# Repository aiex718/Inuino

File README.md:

# Inuino
An Arduino Uno compatible microcontroller dev board based on the ATmega644P / ATmega1284P, using official core inside Arduino IDE.

# Usage
Add this link to boards manager

<https://raw.githubusercontent.com/aiex718/Inuino/master/Release/package_inuino_index.json>

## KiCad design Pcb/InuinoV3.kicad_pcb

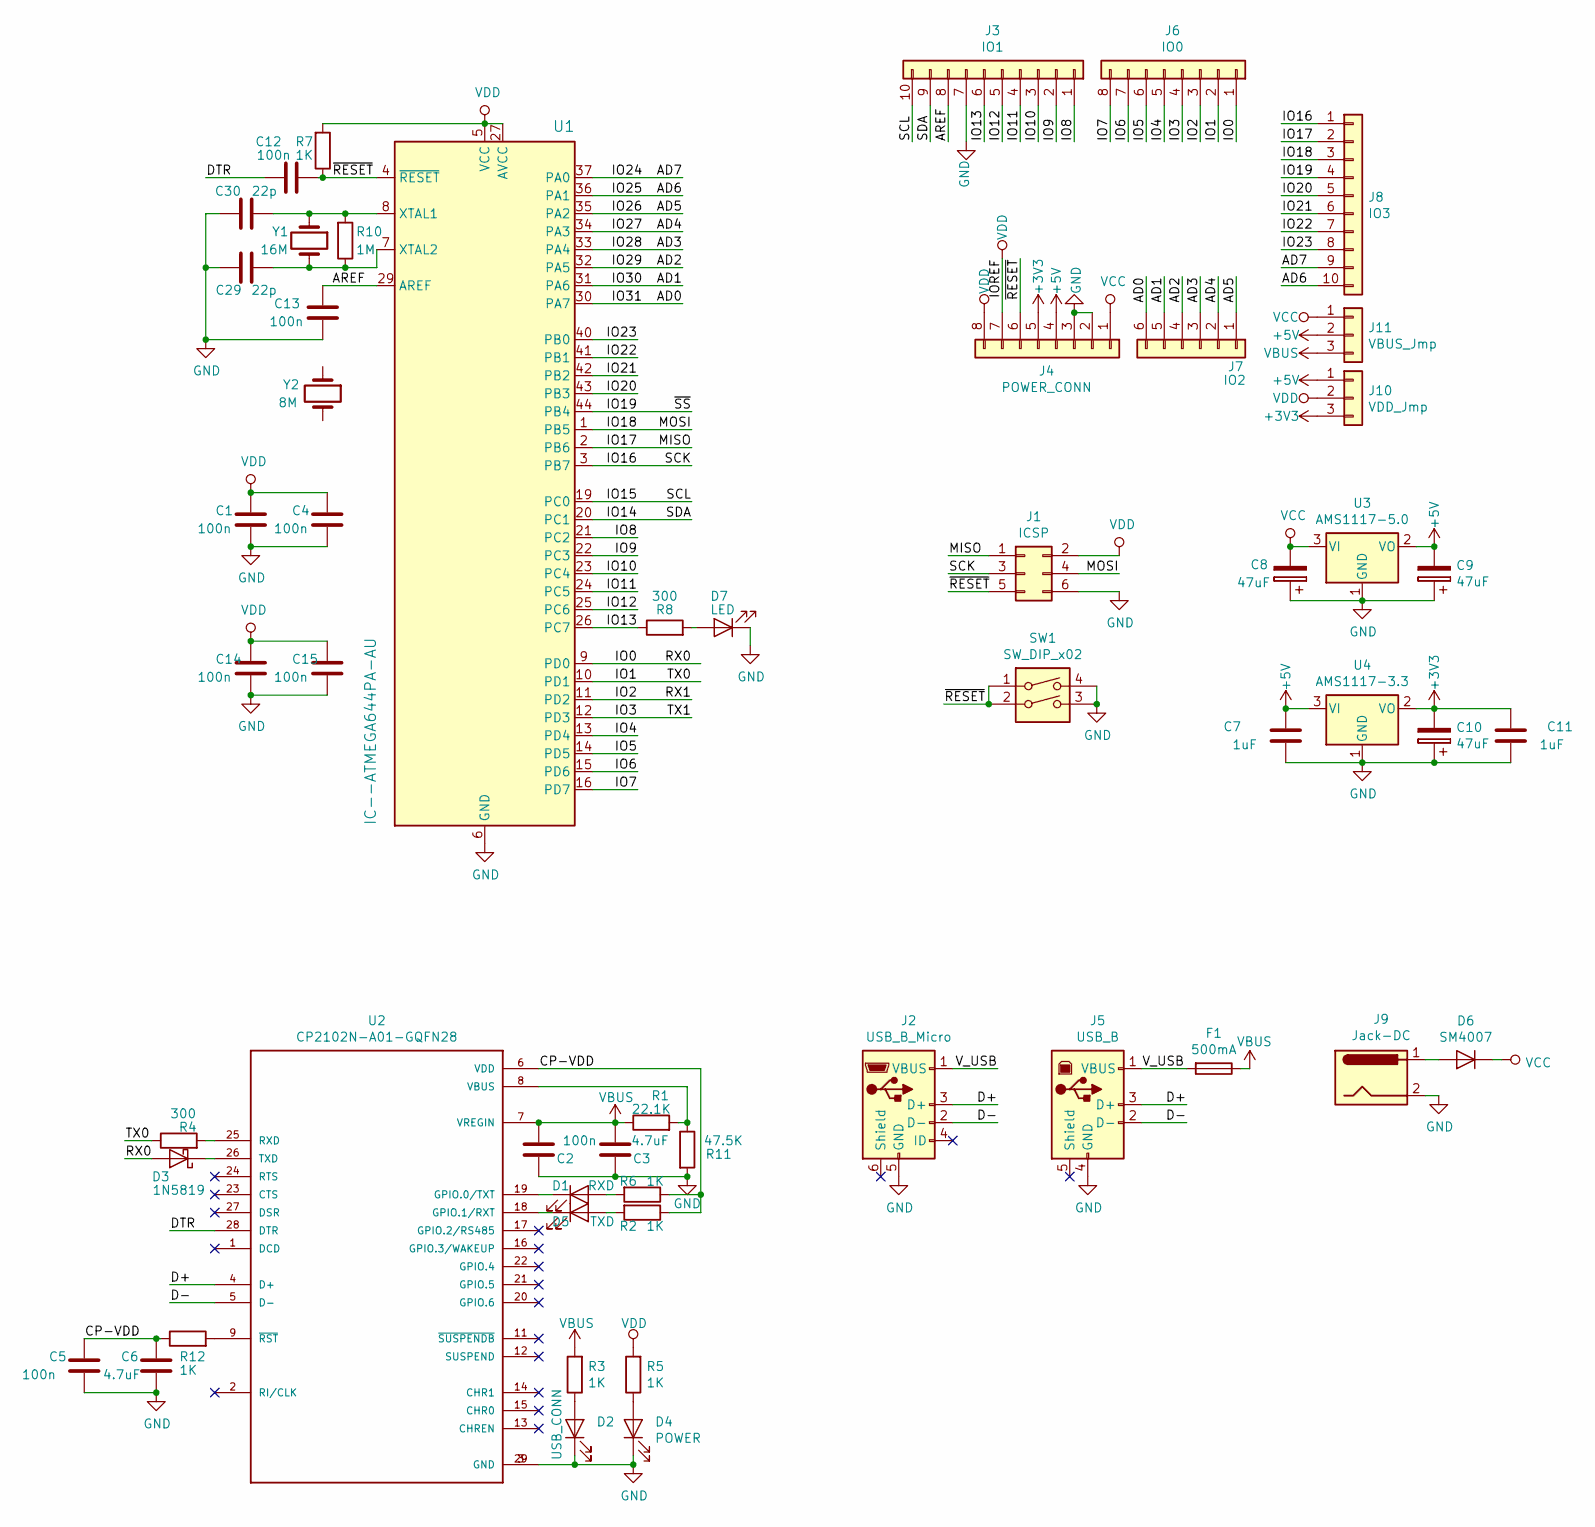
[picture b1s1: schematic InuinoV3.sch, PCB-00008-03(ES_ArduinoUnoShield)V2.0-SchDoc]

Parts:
C1, C2, C4, C5, C12, C13, C14, C15: 100n; C_0805_2012Metric_Pad1.15x1.40mm_HandSolder
C3, C6: 4.7uF; C_0805_2012Metric_Pad1.15x1.40mm_HandSolder
C7, C11: 1uF; C_0805_2012Metric_Pad1.15x1.40mm_HandSolder
C8, C9, C10: 47uF; CP_Radial_D6.3mm_P2.50mm
C29, C30: 22p; C_0805_2012Metric_Pad1.15x1.40mm_HandSolder
D1: RXD; LED_0805_2012Metric_Pad1.15x1.40mm_HandSolder
D2: USB_CONN; LED_0805_2012Metric_Pad1.15x1.40mm_HandSolder
D3: 1N5819; D_SMA_Handsoldering
D4: POWER; LED_0805_2012Metric_Pad1.15x1.40mm_HandSolder
D5: TXD; LED_0805_2012Metric_Pad1.15x1.40mm_HandSolder
D6: SM4007; D_SMA_Handsoldering
D7: LED; LED_0805_2012Metric_Pad1.15x1.40mm_HandSolder
F1: 500mA; Fuse_1812_4532Metric_Pad1.30x3.40mm_HandSolder
J1: ICSP; PinHeader_2x03_P2.54mm_Vertical
J2: USB_B_Micro; USB_Micro-B_Molex-105017-0001
J3: IO1; PinSocket_1x10_P2.54mm_Vertical
J4: POWER_CONN; PinSocket_1x08_P2.54mm_Vertical
J5: USB_B; USB_B_OST_USB-B1HSxx_Horizontal
J6: IO0; PinSocket_1x08_P2.54mm_Vertical
J7: IO2; PinSocket_1x06_P2.54mm_Vertical
J8: IO3; PinSocket_1x10_P2.54mm_Vertical
J9: Jack-DC; BarrelJack_Wuerth_6941xx301002
J10: VDD_Jmp; PinHeader_1x03_P2.54mm_Vertical
J11: VBUS_Jmp; PinHeader_1x03_P2.54mm_Vertical
R1: 22.1K; R_0805_2012Metric_Pad1.15x1.40mm_HandSolder
R2, R3, R5, R6, R7, R12: 1K; R_0805_2012Metric_Pad1.15x1.40mm_HandSolder
R4, R8: 300; R_0805_2012Metric_Pad1.15x1.40mm_HandSolder
R10: 1M; R_0805_2012Metric_Pad1.15x1.40mm_HandSolder
R11: 47.5K; R_0805_2012Metric_Pad1.15x1.40mm_HandSolder
SW1: SW_DIP_x02; SW_TH_Tactile_Omron_B3F-10xx
U1: IC--ATMEGA644PA-AU; LQFP-44_10x10mm_P0.8mm
U2: CP2102N-A01-GQFN28; QFN-28-1EP_5x5mm_P0.5mm_EP3.35x3.35mm_ThermalVias
U3: AMS1117-5.0; SOT-223-3_TabPin2
U4: AMS1117-3.3; SOT-223-3_TabPin2
Y1: 16M; Crystal_HC49-U_Vertical
Y2: 8M; Crystal_HC49-U_Vertical

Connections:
+3V3: C10.2, C11.2, J4.5, J10.3, U4.2 (VO)
+5V: C7.2, C9.2, J4.4, J10.1, J11.2, U3.2 (VO), U4.3 (VI)
/AD0: J7.6, U1.30 (PA7)
/AD1: J7.5, U1.31 (PA6)
/AD2: J7.4, U1.32 (PA5)
/AD3: J7.3, U1.33 (PA4)
/AD4: J7.2, U1.34 (PA3)
/AD5: J7.1, U1.35 (PA2)
/AD6: J8.10, U1.36 (PA1)
/AD7: J8.9, U1.37 (PA0)
/AREF: C13.2, J3.8, U1.29 (AREF)
/CP-VDD: C5.2, C6.2, R2.1, R6.1, R12.1, U2.6 (VDD)
/D+: J2.3 (D+), J5.3 (D+), U2.4 (D+)
/D-: J2.2 (D-), J5.2 (D-), U2.5 (D-)
/DTR: C12.2, U2.28 (DTR)
/IO0: D3.2 (A), J6.1, U1.9 (PD0)
/IO1: J6.2, R4.1, U1.10 (PD1)
/IO2: J6.3, U1.11 (PD2)
/IO3: J6.4, U1.12 (PD3)
/IO4: J6.5, U1.13 (PD4)
/IO5: J6.6, U1.14 (PD5)
/IO6: J6.7, U1.15 (PD6)
/IO7: J6.8, U1.16 (PD7)
/IO8: J3.1, U1.21 (PC2)
/IO9: J3.2, U1.22 (PC3)
/IO10: J3.3, U1.23 (PC4)
/IO11: J3.4, U1.24 (PC5)
/IO12: J3.5, U1.25 (PC6)
/IO13: J3.6, R8.1, U1.26 (PC7)
/IO14: J3.9, U1.20 (PC1)
/IO15: J3.10, U1.19 (PC0)
/IO16: J1.3, J8.1, U1.3 (PB7)
/IO17: J1.1, J8.2, U1.2 (PB6)
/IO18: J1.4, J8.3, U1.1 (PB5)
/IO19: J8.4, U1.44 (PB4)
/IO20: J8.5, U1.43 (PB3)
/IO21: J8.6, U1.42 (PB2)
/IO22: J8.7, U1.41 (PB1)
/IO23: J8.8, U1.40 (PB0)
/V_USB: F1.2, J2.1 (VBUS), J5.1 (VBUS)
/~RESET~: C12.1, J1.5, J4.6, R7.1, SW1.1, SW1.2, U1.4 (~RESET)
GND: C1.1, C2.2, C3.2, C4.1, C5.1, C6.1, C7.1, C8.1, C9.1, C10.1, C11.1, C13.1, C14.1, C15.1, C29.1, C30.2, D2.1 (K), D4.1 (K), D7.1 (K), J1.6, J2.5 (GND), J3.7, J4.2, J4.3, J5.4 (GND), J9.2, R11.2, SW1.3, SW1.4, U1.6 (GND), U1.18 (GND), U1.28 (GND), U1.39 (GND), U2.3 (GND), U2.29 (GND), U3.1 (GND), U4.1 (GND)
unnamed: C29.2, R10.1, U1.7 (XTAL2), Y1.2
unnamed: C30.1, R10.2, U1.8 (XTAL1), Y1.1
unnamed: D1.1 (K), U2.19 (GPIO.0/TXT)
unnamed: D1.2 (A), R6.2
unnamed: D2.2 (A), R3.1
unnamed: D3.1 (K), U2.26 (TXD)
unnamed: D4.2 (A), R5.1
unnamed: D5.1 (K), U2.18 (GPIO.1/RXT)
unnamed: D5.2 (A), R2.2
unnamed: D6.2 (A), J9.1
unnamed: D7.2 (A), R8.2
unnamed: R1.2, R11.1, U2.8 (VBUS)
unnamed: R4.2, U2.25 (RXD)
unnamed: R12.2, U2.9 (~RST~)
VBUS: C2.1, C3.1, F1.1, J11.3, R1.1, R3.2, U2.7 (VREGIN)
VCC: C8.2, D6.1 (K), J4.1, J11.1, U3.3 (VI)
VDD: C1.2, C4.2, C14.2, C15.2, J1.2, J4.7, J4.8, J10.2, R5.2, R7.2, U1.5 (VCC), U1.17 (VCC), U1.27 (AVCC), U1.38 (VCC)

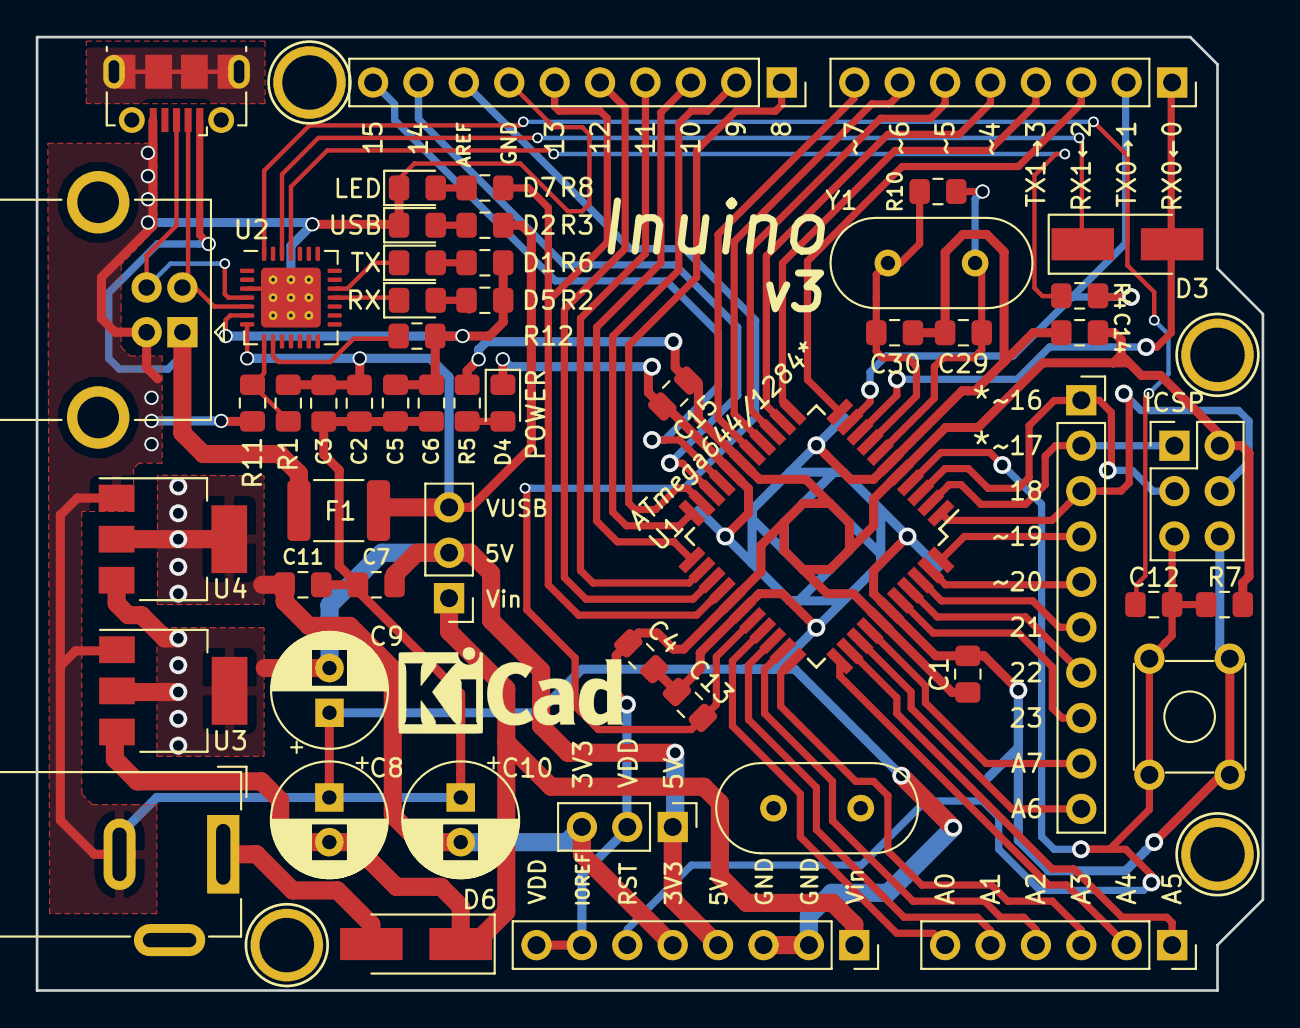
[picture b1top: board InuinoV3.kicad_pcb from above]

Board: 2 copper layers, 68.6 x 53.3 mm, 58 parts (0 on the bottom side), 59 nets.

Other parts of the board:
P5, P6, P7, P8: CONN_01X01; Arduino_1pin

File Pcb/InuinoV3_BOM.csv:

"Id","Designator","Package","Quantity","Designation","Supplier and ref",
1,"REF**","KiCad-Logo_5mm_SilkScreen",1,"KiCad-Logo_5mm_SilkScreen",,,
2,"J11","PinHeader_1x03_P2.54mm_Vertical",1,"VBUS_Jmp",,,
3,"J10","PinHeader_1x03_P2.54mm_Vertical",1,"VDD_Jmp",,,
4,"SW1","SW_TH_Tactile_Omron_B3F-10xx",1,"SW_DIP_x02",,,
5,"C5,C1,C2,C4,C12,C13,C14,C15","C_0805_2012Metric_Pad1.15x1.40mm_HandSolder",8,"100n",,,
6,"U2","QFN-28-1EP_5x5mm_P0.5mm_EP3.35x3.35mm_ThermalVias",1,"CP2102N-A01-GQFN28",,,
7,"R12,R2,R3,R5,R6,R7","R_0805_2012Metric_Pad1.15x1.40mm_HandSolder",6,"1K",,,
8,"R11","R_0805_2012Metric_Pad1.15x1.40mm_HandSolder",1,"47.5K",,,
9,"R10","R_0805_2012Metric_Pad1.15x1.40mm_HandSolder",1,"1M",,,
10,"D4","LED_0805_2012Metric_Pad1.15x1.40mm_HandSolder",1,"POWER",,,
11,"D3","D_SMA_Handsoldering",1,"1N5819",,,
12,"J8","PinSocket_1x10_P2.54mm_Vertical",1,"IO3",,,
13,"Y1","Crystal_HC49-U_Vertical",1,"16M",,,
14,"P5,P6,P7,P8","Arduino_1pin",4,"CONN_01X01",,,
15,"C3,C6","C_0805_2012Metric_Pad1.15x1.40mm_HandSolder",2,"4.7uF",,,
16,"C7,C11","C_0805_2012Metric_Pad1.15x1.40mm_HandSolder",2,"1uF",,,
17,"C8,C9,C10","CP_Radial_D6.3mm_P2.50mm",3,"47uF",,,
18,"C29,C30","C_0805_2012Metric_Pad1.15x1.40mm_HandSolder",2,"22p",,,
19,"D1","LED_0805_2012Metric_Pad1.15x1.40mm_HandSolder",1,"RXD",,,
20,"D2","LED_0805_2012Metric_Pad1.15x1.40mm_HandSolder",1,"USB_CONN",,,
21,"D5","LED_0805_2012Metric_Pad1.15x1.40mm_HandSolder",1,"TXD",,,
22,"D6","D_SMA_Handsoldering",1,"SM4007",,,
23,"F1","Fuse_1812_4532Metric_Pad1.30x3.40mm_HandSolder",1,"500mA",,,
24,"J1","PinHeader_2x03_P2.54mm_Vertical",1,"ICSP",,,
25,"J2","USB_Micro-B_Molex-105017-0001",1,"USB_B_Micro",,,
26,"J3","PinSocket_1x10_P2.54mm_Vertical",1,"IO1",,,
27,"J4","PinSocket_1x08_P2.54mm_Vertical",1,"POWER_CONN",,,
28,"J5","USB_B_OST_USB-B1HSxx_Horizontal",1,"USB_B",,,
29,"J6","PinSocket_1x08_P2.54mm_Vertical",1,"IO0",,,
30,"J7","PinSocket_1x06_P2.54mm_Vertical",1,"IO2",,,
31,"J9","BarrelJack_Wuerth_6941xx301002",1,"Jack-DC",,,
32,"R1","R_0805_2012Metric_Pad1.15x1.40mm_HandSolder",1,"22.1K",,,
33,"R4,R8","R_0805_2012Metric_Pad1.15x1.40mm_HandSolder",2,"300",,,
34,"U3","SOT-223-3_TabPin2",1,"AMS1117-5.0",,,
35,"U4","SOT-223-3_TabPin2",1,"AMS1117-3.3",,,
36,"Y2","Crystal_HC49-U_Vertical",1,"8M",,,
37,"U1","LQFP-44_10x10mm_P0.8mm",1,"IC--ATMEGA644PA-AU",,,
38,"D7","LED_0805_2012Metric_Pad1.15x1.40mm_HandSolder",1,"LED",,,

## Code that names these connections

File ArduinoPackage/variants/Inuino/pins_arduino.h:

/*
  pins_arduino.h - Pin definition functions for Arduino
  Part of Arduino - http://www.arduino.cc/

  Copyright (c) 2007 David A. Mellis

  This library is free software; you can redistribute it and/or
  modify it under the terms of the GNU Lesser General Public
  License as published by the Free Software Foundation; either
  version 2.1 of the License, or (at your option) any later version.

  This library is distributed in the hope that it will be useful,
  but WITHOUT ANY WARRANTY; without even the implied warranty of
  MERCHANTABILITY or FITNESS FOR A PARTICULAR PURPOSE.  See the GNU
  Lesser General Public License for more details.

  You should have received a copy of the GNU Lesser General
  Public License along with this library; if not, write to the
  Free Software Foundation, Inc., 59 Temple Place, Suite 330,
  Boston, MA  02111-1307  USA
*/

#ifndef Pins_Arduino_h
#define Pins_Arduino_h

#include <avr/pgmspace.h>

#define NUM_DIGITAL_PINS            32
#define NUM_ANALOG_INPUTS           8

//Set SPI and I2C to digital pins
static const uint8_t SS   = 19;
static const uint8_t MOSI = 18;
static const uint8_t MISO = 17;
static const uint8_t SCK  = 16;

static const uint8_t SDA = 14;
static const uint8_t SCL = 15;

//Set LED_BUILTIN to digital pins
#define LED_BUILTIN 13

//Set analog pins to digital pins
static const uint8_t A0 = 31;
static const uint8_t A1 = 30;
static const uint8_t A2 = 29;
static const uint8_t A3 = 28;
static const uint8_t A4 = 27;
static const uint8_t A5 = 26;
static const uint8_t A6 = 25;
static const uint8_t A7 = 24;


//Set analog pins to digital pins, A?=D?
#define analogInputToDigitalPin(p)  ((p < NUM_ANALOG_INPUTS) ? 31 - (p) : -1)



//Set which digital pins has pwm(timer)
#if defined(__AVR_ATmega644P__)
#define digitalPinHasPWM(p)         ((p) == 4 || (p) == 5 || (p) == 6 || (p) == 7 || (p) == 19 || (p) == 20)
#elif defined(__AVR_ATmega1284P__)
#define digitalPinHasPWM(p)         ((p) == 4 || (p) == 5 || (p) == 6 || (p) == 7 || (p) == 16 || (p) == 17 || (p) == 19 || (p) == 20)
#endif


// Set digitalPin To PCICR
// p.s. All digitalPin on 644p/1284p has PCICR
#define digitalPinToPCICR(p)    (((p) >= 0 && (p) < NUM_DIGITAL_PINS) ? (&PCICR) : ((uint8_t *)0)) 

// Set digitalPin To PCICR bit
// PortD = 3,PortC = 2,PortB = 1,PortA = 0
#define digitalPinToPCICRbit(p) (((p) <= 7) ? 3 : (((p) <= 15) ? 2 : (((p) <= 23) ? 1 : 0)))

// Set digitalPin To PCMSK 
// PortD = &PCMSK3,PortC = &PCMSK2,PortB = &PCMSK1,PortA = &PCMSK0
#define digitalPinToPCMSK(p)    (((p) <= 7) ? (&PCMSK3) : (((p) <= 15) ? (&PCMSK2) : (((p) <= 23) ? (&PCMSK1) : (&PCMSK0))))  


// Set digitalPin To PCMSK bit
// Relative to digital_pin_to_port_PGM and digital_pin_to_bit_mask_PGM
#define digitalPinToPCMSKbit(p) (((p) <= 7) ? ((p) % 8) : (((p) <= 13) ? ( (p) - 6 ) : (((p) <= 15) ? ( 15 - (p)) : (((p)<=23)?( 23 - (p) ):((p) % 8))))) 

//Set which digital pins has interrupt
#define digitalPinToInterrupt(p)  ((p) == 2 ? 0 : ((p) == 3 ? 1 : ((p) == 21 ? 2 : NOT_AN_INTERRUPT)))


#ifdef ARDUINO_MAIN


// these arrays map port names (e.g. port B) to the
// appropriate addresses for various functions (e.g. reading
// and writing)
const uint16_t PROGMEM port_to_mode_PGM[] = {
	NOT_A_PORT,
	(uint16_t) &DDRA,
	(uint16_t) &DDRB,
	(uint16_t) &DDRC,
	(uint16_t) &DDRD,
};

const uint16_t PROGMEM port_to_output_PGM[] = {
	NOT_A_PORT,
	(uint16_t) &PORTA,
	(uint16_t) &PORTB,
	(uint16_t) &PORTC,
	(uint16_t) &PORTD,
};

const uint16_t PROGMEM port_to_input_PGM[] = {
	NOT_A_PORT,
	(uint16_t) &PINA,
	(uint16_t) &PINB,
	(uint16_t) &PINC,
	(uint16_t) &PIND,
};

const uint8_t PROGMEM digital_pin_to_port_PGM[] = {
	PD, //D0
	PD,
	PD,
	PD,
	PD,
	PD,
	PD,
	PD,
	PC, //D8
	PC,
	PC,
	PC,
	PC,
	PC,
	PC, 
	PC,
	PB, //D16
	PB,
	PB,
	PB,
	PB,
	PB,
	PB,
	PB,
	PA, //D24,AD7
	PA,
	PA,
	PA,
	PA,
	PA,
	PA,
	PA
};

const uint8_t PROGMEM digital_pin_to_bit_mask_PGM[] = {
	_BV(0), // D0 , port D0
	_BV(1), // D1 , port D1
	_BV(2), // D2 , port D2
	_BV(3), // D3 , port D3
	_BV(4), // D4 , port D4
	_BV(5), // D5 , port D5
	_BV(6), // D6 , port D6
	_BV(7), // D7 , port D7
	_BV(2), // D8 , port C2
	_BV(3), // D9 , port C3
	_BV(4), // D10, port C4
	_BV(5), // D11, port C5
	_BV(6), // D12, port C6
	_BV(7), // D13, port C7
	_BV(1), // D14, port C1
	_BV(0), // D15, port C0
	_BV(7), // D16, port B7
	_BV(6), // D17, port B6
	_BV(5), // D18, port B5
	_BV(4), // D19, port B4
	_BV(3), // D20, port B3
	_BV(2), // D21, port B2
	_BV(1), // D22, port B1
	_BV(0), // D23, port B0
	_BV(0), // D24 AD7, port A0
	_BV(1), // D25 AD6, port A1
	_BV(2), // D26 AD5, port A2
	_BV(3), // D27 AD4, port A3
	_BV(4), // D28 AD3, port A4
	_BV(5), // D29 AD2, port A5
	_BV(6), // D30 AD1, port A6
	_BV(7)  // D31 AD0, port A7
};



#if defined(__AVR_ATmega644P__)
const uint8_t PROGMEM digital_pin_to_timer_PGM[] =
{
	NOT_ON_TIMER, 	//D0	 PD0
	NOT_ON_TIMER, 	//D1	 PD1
	NOT_ON_TIMER, 	//D2	 PD2
	NOT_ON_TIMER,   //D3	 PD3
	TIMER1B,		//D4	 PD4
	TIMER1A,	 	//D5	 PD5
	TIMER2B,	 	//D6	 PD6
	TIMER2A,		//D7	 PD7
	
	NOT_ON_TIMER, 	//D8	 PC2
	NOT_ON_TIMER,   //D9	 PC3
	NOT_ON_TIMER,   //D10	 PC4
	NOT_ON_TIMER,	//D11	 PC5
	NOT_ON_TIMER,	//D12	 PC6
	NOT_ON_TIMER,   //D13	 PC7
	NOT_ON_TIMER,  	//D14	 PC1
	NOT_ON_TIMER,  	//D15	 PC0
	
	NOT_ON_TIMER, 	//D16	 PB7
	NOT_ON_TIMER, 	//D17	 PB6
	NOT_ON_TIMER, 	//D18	 PB5
	TIMER0B, 		//D19	 PB4
	TIMER0A,   		//D20	 PB3
	NOT_ON_TIMER,   //D21	 PB2
	NOT_ON_TIMER,   //D22	 PB1
	NOT_ON_TIMER,   //D23	 PB0
	
	NOT_ON_TIMER,   //D24	 PA0
	NOT_ON_TIMER,   //D25	 PA1
	NOT_ON_TIMER,   //D26	 PA2
	NOT_ON_TIMER,   //D27	 PA3
	NOT_ON_TIMER,   //D28	 PA4
	NOT_ON_TIMER,   //D29	 PA5
	NOT_ON_TIMER,   //D30	 PA6
	NOT_ON_TIMER    //D31	 PA7
};

#elif defined(__AVR_ATmega1284P__)

const uint8_t PROGMEM digital_pin_to_timer_PGM[] =
{
	NOT_ON_TIMER, 	//D0	 PD0
	NOT_ON_TIMER, 	//D1	 PD1
	NOT_ON_TIMER, 	//D2	 PD2
	NOT_ON_TIMER,   //D3	 PD3
	TIMER1B,		//D4	 PD4
	TIMER1A,	 	//D5	 PD5
	TIMER2B,	 	//D6	 PD6
	TIMER2A,		//D7	 PD7
	
	NOT_ON_TIMER, 	//D8	 PC2
	NOT_ON_TIMER,   //D9	 PC3
	NOT_ON_TIMER,   //D10	 PC4
	NOT_ON_TIMER,	//D11	 PC5
	NOT_ON_TIMER,	//D12	 PC6
	NOT_ON_TIMER,   //D13	 PC7
	NOT_ON_TIMER,  	//D14	 PC1
	NOT_ON_TIMER,  	//D15	 PC0
	
	TIMER3B, 		//D16	 PB7
	TIMER3A, 		//D17	 PB6
	NOT_ON_TIMER, 	//D18	 PB5
	TIMER0B, 		//D19	 PB4
	TIMER0A,   		//D20	 PB3
	NOT_ON_TIMER,   //D21	 PB2
	NOT_ON_TIMER,   //D22	 PB1
	NOT_ON_TIMER,   //D23	 PB0
	
	NOT_ON_TIMER,   //D24	 PA0
	NOT_ON_TIMER,   //D25	 PA1
	NOT_ON_TIMER,   //D26	 PA2
	NOT_ON_TIMER,   //D27	 PA3
	NOT_ON_TIMER,   //D28	 PA4
	NOT_ON_TIMER,   //D29	 PA5
	NOT_ON_TIMER,   //D30	 PA6
	NOT_ON_TIMER    //D31	 PA7
};
#endif //Timer define






#endif //Arduino Main

// These serial port names are intended to allow libraries and architecture-neutral
// sketches to automatically default to the correct port name for a particular type
// of use.  For example, a GPS module would normally connect to SERIAL_PORT_HARDWARE_OPEN,
// the first hardware serial port whose RX/TX pins are not dedicated to another use.
//
// SERIAL_PORT_MONITOR        Port which normally prints to the Arduino Serial Monitor
//
// SERIAL_PORT_USBVIRTUAL     Port which is USB virtual serial
//
// SERIAL_PORT_LINUXBRIDGE    Port which connects to a Linux system via Bridge library
//
// SERIAL_PORT_HARDWARE       Hardware serial port, physical RX & TX pins.
//
// SERIAL_PORT_HARDWARE_OPEN  Hardware serial ports which are open for use.  Their RX & TX
//                            pins are NOT connected to anything by default.
#define SERIAL_PORT_MONITOR   Serial
#define SERIAL_PORT_HARDWARE  Serial

#endif

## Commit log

2019-02-23 Update LICENSE
2019-02-23 Initial release
2019-02-23 edit release json
